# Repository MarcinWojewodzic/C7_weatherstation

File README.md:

# C7_weatherstation
Simple weather station with e-inc display with measurement memory based on PMS3003 and BME688 sensors

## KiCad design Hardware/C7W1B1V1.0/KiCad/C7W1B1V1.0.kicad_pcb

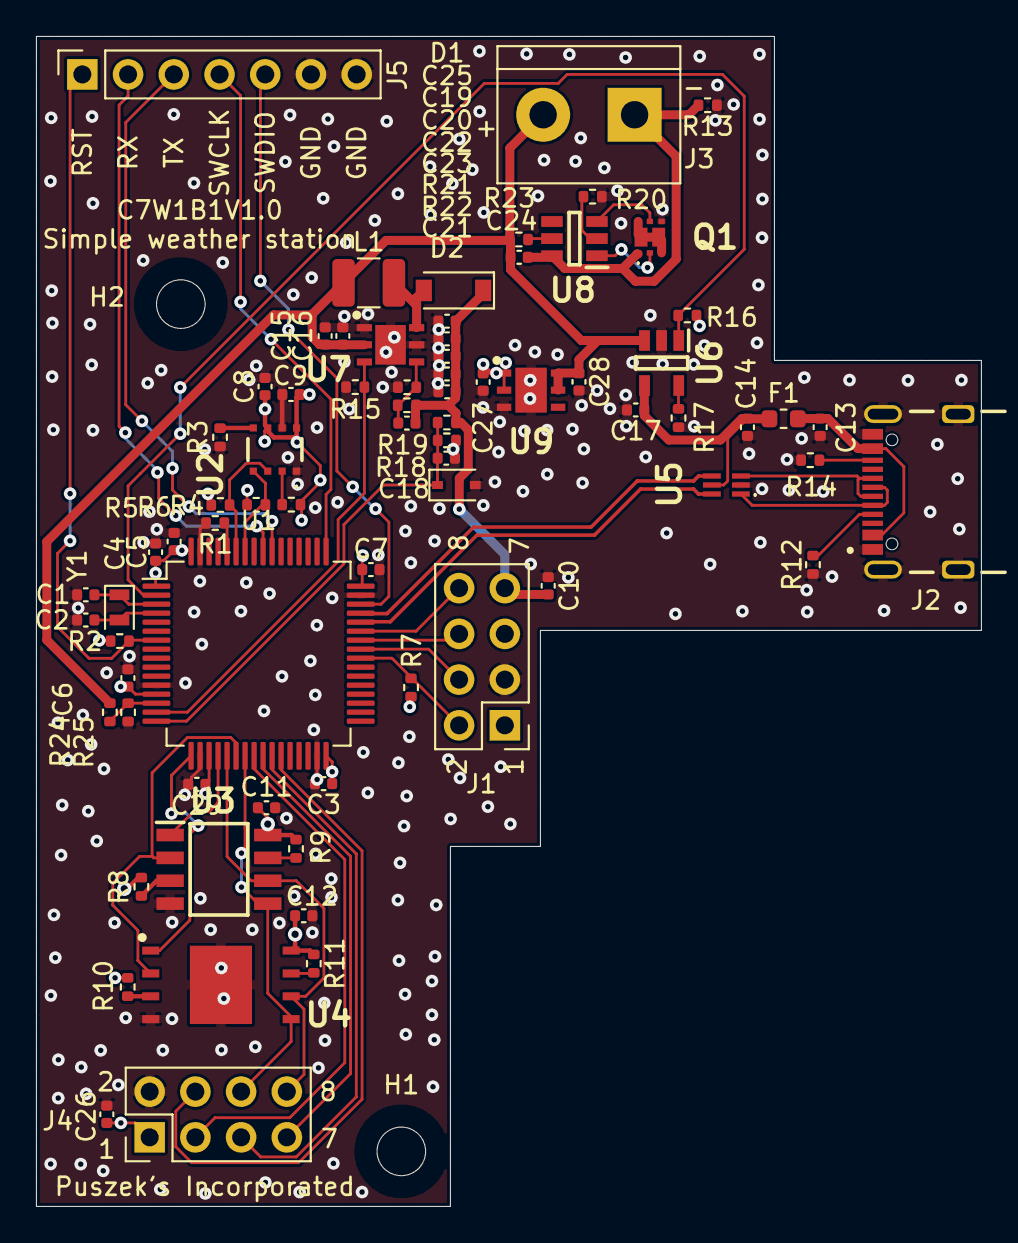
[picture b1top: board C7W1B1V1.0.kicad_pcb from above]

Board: 4 copper layers, 52.5 x 65.0 mm, 76 parts (0 on the bottom side), 54 nets.

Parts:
C1, C2: 8p/16V/C0G; C_0402_1005Metric
C3, C4, C5, C6, C7, C8, C9, C10, C11, C12, C24, C25, C26, C29: 100n/16V/X5R; C_0402_1005Metric
C13, C14, C15, C16, C17, C19, C20, C22, C23, C27, C28: 10u/6.3V/X5R; C_0402_1005Metric
C18: 510p/10V/C0G; C_0402_1005Metric
C21: 10n/16V/X5R; C_0402_1005Metric
D1: PMEG4010CEGWX; D_SOD-123
D2: BZX384B3V3-E3-08; D_SOD-323
F1: 0686F2000-01; Fuse_0603_1608Metric
H1, H2: MountingHole; MountingHole_2.7mm_M2.5
J1: PMS3003; PinHeader_2x04_P2.54mm_Vertical
J2: USB4105GFA120; GCT_USB4105GFA120
J3: Conn_01x02_Male; TerminalBlock_bornier-2_P5.08mm
J4: Waveshare 12955; PinHeader_2x04_P2.54mm_Vertical
J5: Conn_01x07; PinSocket_1x07_P2.54mm_Vertical
L1: CBC3225T470MR; L_1210_3225Metric
Q1: PMDPB30XNAX
R1, R2, R3, R4, R5, R6, R7, R8, R9, R10, R11, R12, R14, R15, R16: 10k/5%/0.063W; R_0402_1005Metric
R13: 0R; R_0402_1005Metric
R17, R20: 2k2/5%/0.063W; R_0402_1005Metric
R18: 30k/1%/0.063W; R_0402_1005Metric
R19, R21, R22: 10k/1%/0.063W; R_0402_1005Metric
R23: 470R/5%/0.063W; R_0402_1005Metric
R24, R25: 100k/1%/0.063W; R_0402_1005Metric
U1: STM32L083RZTx; LQFP-64_10x10mm_P0.5mm
U2: BME688
U3: MB85RS512TPNF-G-JNERE1; SOIC127P600X175-8N
U4: W25N512GVEIG; SON127P800X600X80-9N-D
U5: USBLC6-2P6; USBLC62P6
U6: STC4054GR; SOT95P280X110-5N
U7: LMR62421XSD_NOPB; SON95P300X300X80-7N
U8: S-8261AAXMD-G2XT2U; SOT95P275X135-6N
U9: LD39200PU33R; SON95P300X300X100-7N-D
Y1: 830106545501; Crystal_SMD_2012-2Pin_2.0x1.2mm

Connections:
5V_EN: R15.1, U1.15, U7.3
5V_TEST: C21.1, D2.1, R21.2, R22.1, U1.16
+3V3: C3.1, C4.1, C5.1, C6.1, C7.1, C8.1, C9.1, C11.1, C12.1, C26.2, C27.1, C29.1, J4.1, R2.1, R4.1, R5.1, R6.1, R7.1, R8.1, R9.1, R10.1, R11.1, R16.1, U1.1, U1.13, U1.19, U1.32, U1.48, U1.64, U2.6, U2.8, U3.8, U4.8, U9.1, U9.2
+5V: C10.2, C18.1, C19.1, C20.1, C22.1, C23.1, C25.1, D1.1, J1.7, R18.1, R21.1
+BATT: C15.1, C16.1, C24.1, C28.1, J3.2, L1.1, R23.2, R24.1, U6.3, U7.2, U9.5, U9.6
/Power/USB_VBUS: C13.1, F1.2, J2.A4_B9, J2.B4_A9
BATT: R24.2, R25.1, U1.14
E_INC_BUSY: J4.5, U1.26
E_INC_CS: J4.3, U1.24
E_INC_DC: J4.4, U1.27
E_INC_RST: J4.7, U1.25
GND: C1.1, C2.1, C3.2, C4.2, C5.2, C6.2, C7.2, C8.2, C9.2, C10.1, C11.2, C12.2, C13.2, C14.2, C15.2, C16.2, C17.2, C19.2, C20.2, C21.2, C22.2, C23.2, C25.2, C26.1, C27.2, C28.2, C29.2, D2.2, J1.3, J2.A1_B12, J2.B1_A12, J2.SH1, J2.SH2, J2.SH3, J2.SH4, J4.2, J5.6, J5.7, Q1.4, R1.2, R3.2, R12.1, R13.1, R14.1, R15.2, R17.2, R19.2, R20.2, R22.2, R25.2, U1.12, U1.18, U1.31, U1.47, U1.63, U2.1, U2.7, U3.4, U4.4, U4.9, U5.2, U6.2, U7.1, U7.5, U7.7, U9.3, U9.7
GND1: C24.2, J3.1, Q1.1, R13.2, U8.6
MISO: U1.22, U3.2, U4.2
MOSI: J4.6, U1.23, U3.5, U4.5
unnamed: C1.2, U1.3, Y1.1
unnamed: C2.2, U1.4, Y1.2
unnamed: C18.2, R18.2, R19.1, U7.4
unnamed: D1.2, L1.2, U7.6
unnamed: J2.A5, R12.2
unnamed: J2.A6, J2.B6, U5.3
unnamed: J2.A7, J2.B7, U5.1
unnamed: J2.B5, R14.2
unnamed: Q1.2, U8.1
unnamed: Q1.3, Q1.6, Q1.7, Q1.8
unnamed: Q1.5, U8.3
unnamed: R1.1, U1.60
unnamed: R3.1, U2.5
unnamed: R4.2, U2.2
unnamed: R8.2, U3.3
unnamed: R9.2, U3.7
unnamed: R10.2, U4.3
unnamed: R11.2, U4.7
unnamed: R17.1, U6.5
unnamed: R20.1, U8.2
unnamed: R23.1, U8.5
PMS_RST: J1.4, U1.41
PMS_RX: J1.6, U1.42
PMS_SET: J1.2, R7.2, U1.40
PMS_TX: J1.8, U1.43
RST: J5.1, R2.2, U1.7
RX: J5.2, U1.56
SCK: J4.8, U1.21, U3.6, U4.6
SCL: R6.2, U1.58, U2.4
SDA: R5.2, U1.59, U2.3
SWCLK: J5.4, U1.49
SWDIO: J5.5, U1.46
TX: J5.3, U1.55
USB_D+: U1.45, U5.4
USB_D-: U1.44, U5.6
VBUS: C14.1, C17.1, F1.1, U5.5, U6.4
~CHRG_STATUS: R16.2, U1.2, U6.1
~FLASH_CS: U1.17, U4.1
~FRAM_CS: U1.20, U3.1

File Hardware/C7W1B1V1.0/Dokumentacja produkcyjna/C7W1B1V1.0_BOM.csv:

"Id";"Oznaczenie";"Obudowa";"Ilość";"Oznaczenie";"Dostawca i numer artykułu";
1;"H2,H1";"MountingHole_2.7mm_M2.5";2;"MountingHole";;;
2;"J5";"PinSocket_1x07_P2.54mm_Vertical";1;"Conn_01x07";;;
3;"U9";"SON95P300X300X100-7N-D";1;"LD39200PU33R";;;
4;"C28,C27,C14,C13,C17,C23,C22,C20,C19,C16,C15";"C_0402_1005Metric";11;"10u/6.3V/X5R";;;
5;"U5";"USBLC62P6";1;"USBLC6-2P6";;;
6;"R25,R24";"R_0402_1005Metric";2;"100k/1%/0.063W";;;
7;"R14,R12,R16,R15,R7,R6,R5,R4,R3,R2,R1,R11,R10,R9,R8";"R_0402_1005Metric";15;"10k/5%/0.063W";;;
8;"R13";"R_0402_1005Metric";1;"0R";;;
9;"J2";"GCT_USB4105GFA120";1;"USB4105GFA120";;;
10;"F1";"Fuse_0603_1608Metric";1;"0686F2000-01";;;
11;"U6";"SOT95P280X110-5N";1;"STC4054GR";;;
12;"R17,R20";"R_0402_1005Metric";2;"2k2/5%/0.063W";;;
13;"J3";"TerminalBlock_bornier-2_P5.08mm";1;"Conn_01x02_Male";;;
14;"U8";"SOT95P275X135-6N";1;"S-8261AAXMD-G2XT2U";;;
15;"Q1";"PMDPB30XNAX";1;"PMDPB30XNAX";;;
16;"R23";"R_0402_1005Metric";1;"470/5%/0.063W";;;
17;"C24,C25,C10,C9,C8,C7,C6,C5,C4,C3,C12,C11,C26";"C_0402_1005Metric";13;"100n/16V/X5R";;;
18;"U7";"SON95P300X300X80-7N";1;"LMR62421XSD_NOPB";;;
19;"R22,R21,R19";"R_0402_1005Metric";3;"10k/1%/0.063W";;;
20;"R18";"R_0402_1005Metric";1;"30k/1%/0.063W";;;
21;"L1";"L_1210_3225Metric";1;"CBC3225T470MR";;;
22;"D2";"D_SOD-323";1;"BZX384B3V3-E3-08";;;
23;"D1";"D_SOD-123";1;"PMEG4010CEGWX";;;
24;"C21";"C_0402_1005Metric";1;"10n/16V/X5R";;;
25;"C18";"C_0402_1005Metric";1;"510p/10V/C0G";;;
26;"J1";"PinHeader_2x04_P2.54mm_Vertical";1;"PMS3003";;;
27;"U2";"BME688";1;"BME688";;;
28;"Y1";"Crystal_SMD_2012-2Pin_2.0x1.2mm";1;"830106545501";;;
29;"C2,C1";"C_0402_1005Metric";2;"8p/16V/C0G";;;
30;"J4";"PinHeader_2x04_P2.54mm_Vertical";1;"Waveshare 12955";;;
31;"U1";"LQFP-48_7x7mm_P0.5mm";1;"STM32L083CZTx";;;
32;"U4";"SON127P800X600X80-9N-D";1;"W25N512GVEIG";;;
33;"U3";"SOIC127P600X175-8N";1;"MB85RS512TPNF-G-JNERE1";;;

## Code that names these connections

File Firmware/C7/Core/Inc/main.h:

/* USER CODE BEGIN Header */
/**
  ******************************************************************************
  * @file           : main.h
  * @brief          : Header for main.c file.
  *                   This file contains the common defines of the application.
  ******************************************************************************
  * @attention
  *
  * Copyright (c) 2024 STMicroelectronics.
  * All rights reserved.
  *
  * This software is licensed under terms that can be found in the LICENSE file
  * in the root directory of this software component.
  * If no LICENSE file comes with this software, it is provided AS-IS.
  *
  ******************************************************************************
  */
/* USER CODE END Header */

/* Define to prevent recursive inclusion -------------------------------------*/
#ifndef __MAIN_H
#define __MAIN_H

#ifdef __cplusplus
extern "C" {
#endif

/* Includes ------------------------------------------------------------------*/
#include "stm32l0xx_hal.h"

/* Private includes ----------------------------------------------------------*/
/* USER CODE BEGIN Includes */

/* USER CODE END Includes */

/* Exported types ------------------------------------------------------------*/
/* USER CODE BEGIN ET */

/* USER CODE END ET */

/* Exported constants --------------------------------------------------------*/
/* USER CODE BEGIN EC */

/* USER CODE END EC */

/* Exported macro ------------------------------------------------------------*/
/* USER CODE BEGIN EM */

/* USER CODE END EM */

/* Exported functions prototypes ---------------------------------------------*/
void Error_Handler(void);

/* USER CODE BEGIN EFP */

/* USER CODE END EFP */

/* Private defines -----------------------------------------------------------*/
#define SUTATS_GRHC_Pin GPIO_PIN_13
#define SUTATS_GRHC_GPIO_Port GPIOC
#define ON_OFF_5V_Pin GPIO_PIN_2
#define ON_OFF_5V_GPIO_Port GPIOA
#define FLASH_CS_Pin GPIO_PIN_3
#define FLASH_CS_GPIO_Port GPIOA
#define FRAM_CS_Pin GPIO_PIN_4
#define FRAM_CS_GPIO_Port GPIOA
#define E_INC_CS_Pin GPIO_PIN_0
#define E_INC_CS_GPIO_Port GPIOB
#define E_INC_RST_Pin GPIO_PIN_1
#define E_INC_RST_GPIO_Port GPIOB
#define E_INC_BUSY_Pin GPIO_PIN_2
#define E_INC_BUSY_GPIO_Port GPIOB
#define E_INC_DC_Pin GPIO_PIN_10
#define E_INC_DC_GPIO_Port GPIOB
#define PMS_SET_Pin GPIO_PIN_15
#define PMS_SET_GPIO_Port GPIOB
#define PMS_RST_Pin GPIO_PIN_8
#define PMS_RST_GPIO_Port GPIOA

/* USER CODE BEGIN Private defines */

/* USER CODE END Private defines */

#ifdef __cplusplus
}
#endif

#endif /* __MAIN_H */

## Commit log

2024-11-08 początkowy schemat
2024-11-15 Dodano projekt Cube
2024-11-16 Ukończono PCB. dodano pliki produkcyjne
2024-11-16 Zmieniono procesor na wersję LQFP-64
